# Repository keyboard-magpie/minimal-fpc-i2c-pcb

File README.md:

# minimal-fpc-i2c-pcb
Minimal adapter board for converting keyboard i2c oled pins to ffc/fpc ribbon cable for keyboards such as crkbd, kimiko or kyria, intended to make using cirque glidepoint trackpads easier with keyboards that already have an OLED header.

# how to use
To use the TM035035 and TM040040 with 5v controllers, on the back trackpad, remove R1 for I2C, and remove R7 and R8 for 5V (leave these if using with 3v3 controllers i.e. rp2040.

# holders
In the holders folder you will find holders for the curved overlays (35 and 40mm- please note there was an earlier misnaming of these files which I have corrected as of 16 Feb 2023).

# production
Please note there is a small error in the cpl file for the ffc connector that comes from the footprint for it. JLC should correct its placement for you.

Connector used is this one from LCSC: https://lcsc.com/product-detail/FFC-FPC-Connectors_SHENZHEN-ATOM-TECH-FPC05012-09200_C479750.html

# alternative FPC connectors: 
https://www.digikey.co.uk/en/products/detail/hirose-electric-co-ltd/FH12-12S-0.5SH-55/1110374 \
https://www.digikey.co.uk/en/products/detail/gct/FFC2B35-12-G/15970866 \
Both of the above were suggested by u/idyllic on discord and look to have a footprint that is very close the the LCSC part above and should be compatible.

# ffc/fpc cables
Any generic flat flex cable can be used, they are 12 position, 0.5mm pitch, same-sided contacts. The molex extra flex and primo flex series from mouser seem to work well.

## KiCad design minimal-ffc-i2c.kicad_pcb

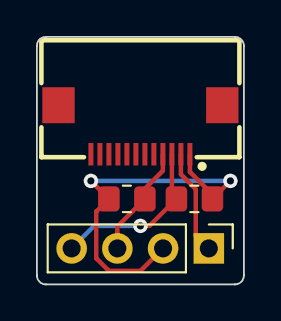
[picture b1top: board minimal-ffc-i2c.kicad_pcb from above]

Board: 2 copper layers, 11.5 x 13.8 mm, 4 parts (0 on the bottom side), 4 nets.

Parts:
J1: Conn_01x04_Female; PinHeader_1x04_P2.54mm_Vertical
J2: Conn_01x12_Female; FPC-SMD_FPC05012-09200-.5mm-rev
R1, R2: 4k7; R_0805_2012Metric_Pad1.20x1.40mm_HandSolder

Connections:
gnd: J1.1, J2.2
sck: J1.3, J2.4, R1.1
sda: J1.4, J2.3, R2.1
vcc: J1.2, J2.1, R1.2, R2.2

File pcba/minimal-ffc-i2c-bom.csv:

Comment,Designator,Footprint,LCSC Part # 
4.7k Resistor,"R1, R2",Resistor_SMD:R_0805_2012Metric_Pad1.20x1.40mm_HandSolder,C441952
12 pin 0.5mm pitch FPC connector,J2,minimal-ffc-i2c:FPC-SMD_FPC05012-09200-.5mm-rev,C479750

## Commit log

2022-07-07 Create license
2022-07-07 add pcba files
2022-07-08 add holder stls
    Holders for the 40mm cirques I've designed
2022-07-09 vcc fix
2022-07-09 add kimiko holder
2022-07-09 yes. something changed.
2023-02-16 fix holder naming errors, update readme, add missing 40mm files
